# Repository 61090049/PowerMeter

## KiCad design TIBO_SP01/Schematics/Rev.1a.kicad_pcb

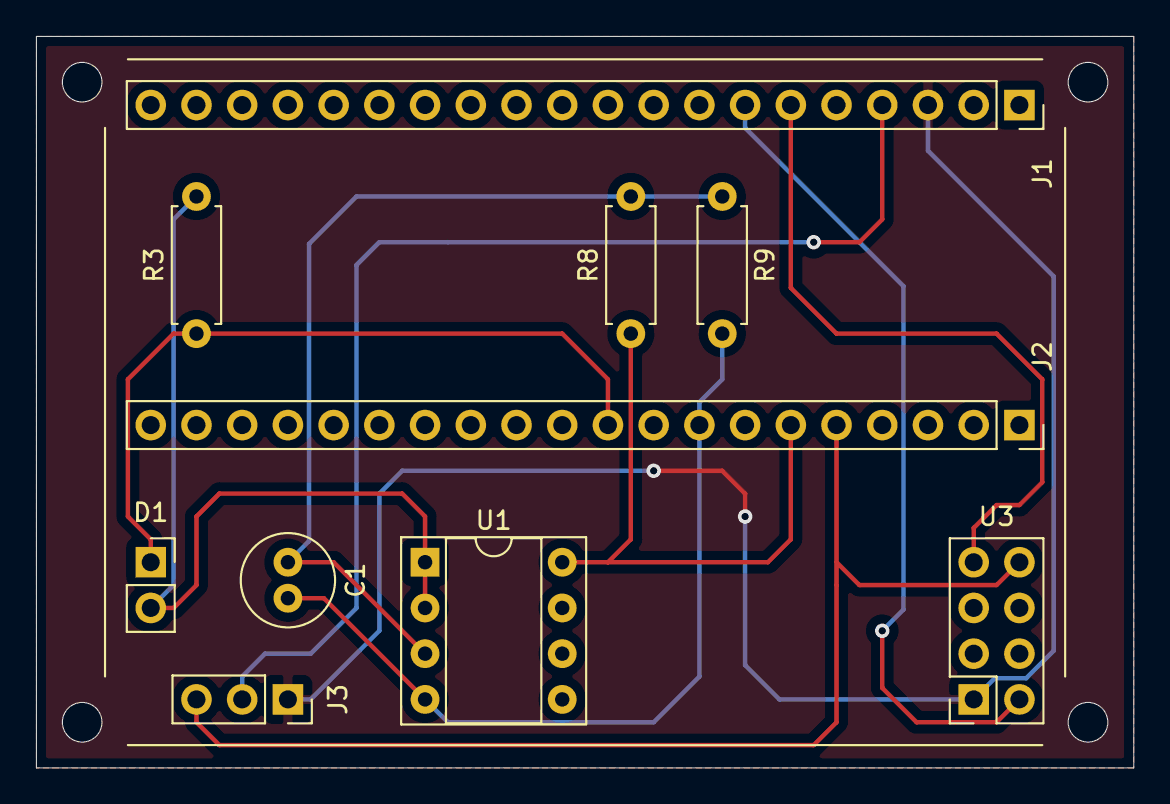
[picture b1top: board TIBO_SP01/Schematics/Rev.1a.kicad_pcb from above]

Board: 2 copper layers, 61.0 x 40.6 mm, 10 parts (0 on the bottom side), 10 nets.

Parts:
C1: 1uF; C_Radial_D5.0mm_H11.0mm_P2.00mm
D1: D_TVS_ALT; PinSocket_1x02_P2.54mm_Vertical
J1: Conn_01x20x2; PinSocket_1x20_P2.54mm_Vertical
J2: RASP_PI_PICO; PinSocket_1x20_P2.54mm_Vertical
J3: Conn_01x03_Female; PinSocket_1x03_P2.54mm_Vertical
R3: 77Ω; R_Axial_DIN0207_L6.3mm_D2.5mm_P7.62mm_Horizontal
R8, R9: 20KΩ; R_Axial_DIN0207_L6.3mm_D2.5mm_P7.62mm_Horizontal
U1: LM358; DIP-8_W7.62mm_Socket
U3: ESP-07; PinSocket_2x04_P2.54mm_Vertical

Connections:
ADC0: D1.1, J2.10, R3.1
ADC_VREF: J2.6, R8.1, U1.8
AGND: C1.2, J2.8, R9.2, U1.4
GND: J1.3, J3.1, U3.1
IN1: J1.4, J3.2
unnamed: C1.1, R8.2, R9.1, U1.3
unnamed: D1.2, R3.2, U1.1, U1.2
UART1_RX: J1.7, U3.2
UART1_TX: J1.6, U3.7
VCC: J2.5, J3.3, U3.8

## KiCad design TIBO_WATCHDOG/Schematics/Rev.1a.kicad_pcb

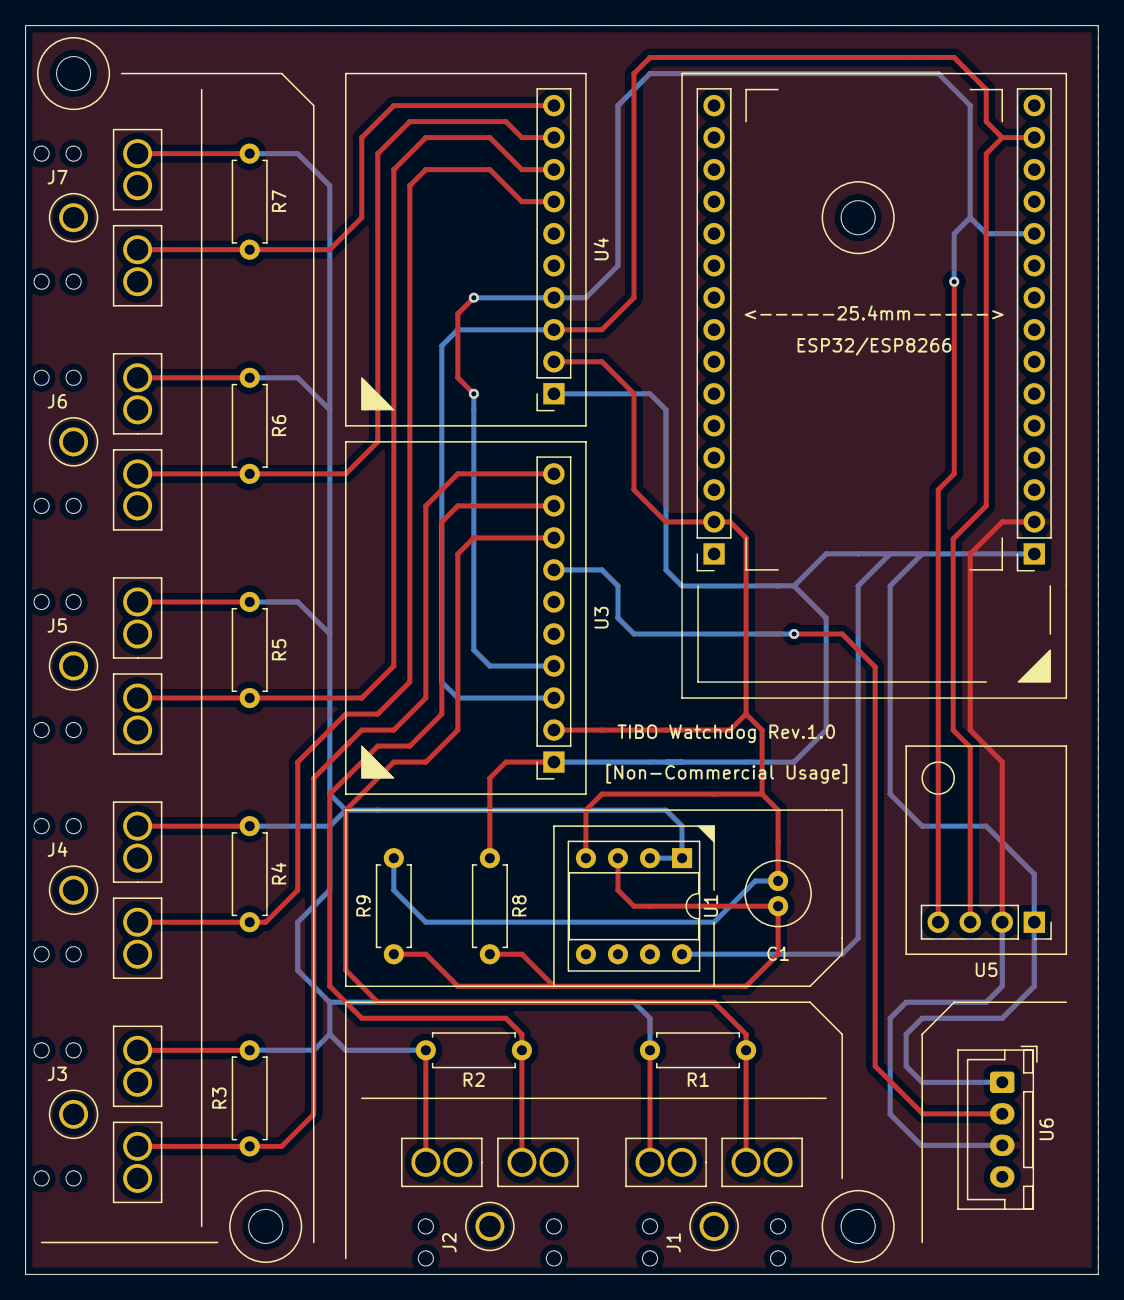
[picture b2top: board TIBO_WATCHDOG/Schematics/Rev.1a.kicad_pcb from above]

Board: 2 copper layers, 85.1 x 99.1 mm, 24 parts (0 on the bottom side), 15 nets.

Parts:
<-----25.4mm----->: Conn_01x15_MountingPin; PinSocket_1x15_P2.54mm_Vertical
C1: 10uF; C_Radial_D5.0mm_H11.0mm_P2.00mm
ESP32/ESP8266: CONN_HEADER_2X15; PinSocket_1x15_P2.54mm_Vertical
J1, J2, J3, J4, J5, J6, J7: AudioJack2_Ground; Sparkfun_Audio_Jack_3.5mm
R1, R2, R3, R4, R5, R6, R7: 77Ω; R_Axial_DIN0207_L6.3mm_D2.5mm_P7.62mm_Horizontal
R8, R9: 20KΩ; R_Axial_DIN0207_L6.3mm_D2.5mm_P7.62mm_Horizontal
U1: .; DIP-8_W7.62mm_Socket
U3, U4: ADS1115IDGS; PinSocket_1x10_ADS1115
U5: AHT10; PinSocket_1x04_P2.54mm_Vertical
U6: ZMPT101B; JST_XH_B4B-XH-A_1x04_P2.50mm_Vertical

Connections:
unnamed: C1.1, R8.2, R9.1, U1.3
unnamed: C1.2, ESP32/ESP8266.2, R9.2, U1.4, U3.3, U4.3
unnamed: J1.S, R1.1, U3.5
unnamed: J1.T, J2.T, J3.T, J4.T, J5.T, J6.T, J7.T, R1.2, R2.2, R3.2, R4.1, R5.1, R6.1, R7.1, U1.1, U1.2
unnamed: J2.S, R2.1, U3.6
unnamed: J3.S, R3.1, U3.7
unnamed: J4.S, R4.2, U4.4
unnamed: J5.S, R5.2, U4.5
unnamed: J6.S, R6.2, U4.6
unnamed: J7.S, R7.2, U4.7
unnamed: <-----25.4mm----->.1, R8.1, U1.8, U3.8, U4.8, U5.1, U6.1
unnamed: <-----25.4mm----->.2, U5.2, U6.3
unnamed: <-----25.4mm----->.11, U3.9, U4.9, U5.4
unnamed: <-----25.4mm----->.14, U3.10, U4.10, U5.3
unnamed: U3.4, U6.2
